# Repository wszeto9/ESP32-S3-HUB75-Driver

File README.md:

# ESP32-S3-HUB75-Driver

This board serves as the Matrix Display driver for MIT's 2.007 gameboards in Spring 2024 and Spring 2025. The board can take 4 button inputs, Stemma-QT I2C sensors, and breaks out 8 GPIO pins for future use. The board also features a ambient light sensor to adjust brightness in real time, as well as two buttons to switch modes if needed. The board supports USB-C PD power input up to 20V and USB debugging, as well as a 5.5mm OD / 2.1mm ID barrel jack for 9-24V input. A 5V/6A Buck converter helps ensure that the display is adequately powered. For this reason, it's recommended to power the display off a source higher than 5V for long term purposes. 

The board contains a power mux that automatically switches power sources based on what's present. It will always choose the first power source that's provided. If debugging is desired, it's recommended to first plug in the barrel jack for power, then use the USB port for debugging. This ensures lower power draw from the host computer. 

Upon power up, D7 or D9 will light up based on what power source is present. D2 should blink in accordance to the voltage of the power source (ie 5 blinks is a 5V source). D1 indicates that power is properly being delivered to the converter. 

At this point, the ESP32-S3 should pop up as a virtual COM port over USB. Boot and reset buttons are located by the ESP, but they may not be needed to perform DFU. 

Note: E8 and E16 refer to the pin that is used to act as pin E. This is only present on 64x64 pixel displays and larger. Some displays use pin 8, some displays use pin 16. Adafruit claims they use pin 8 for address E, so use a solder blob to jump the jumper to E8.

Further documentation can be found under the specific firmware builds.

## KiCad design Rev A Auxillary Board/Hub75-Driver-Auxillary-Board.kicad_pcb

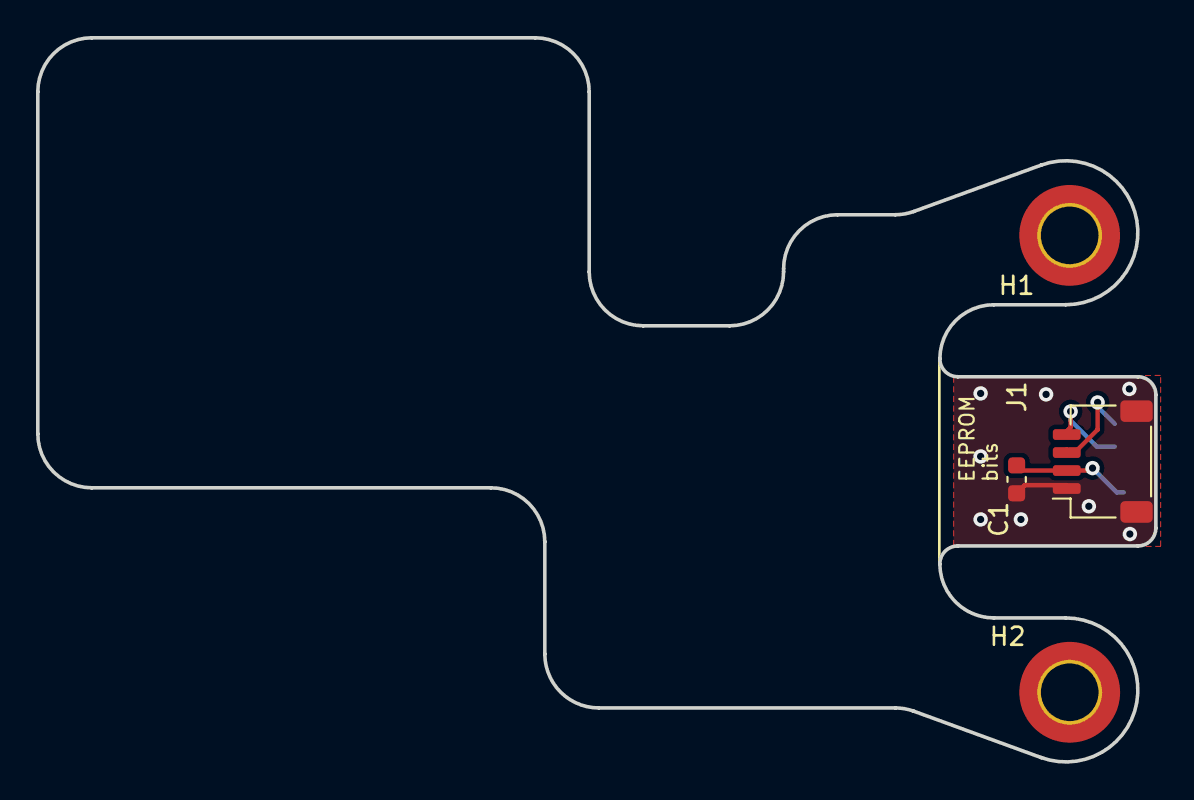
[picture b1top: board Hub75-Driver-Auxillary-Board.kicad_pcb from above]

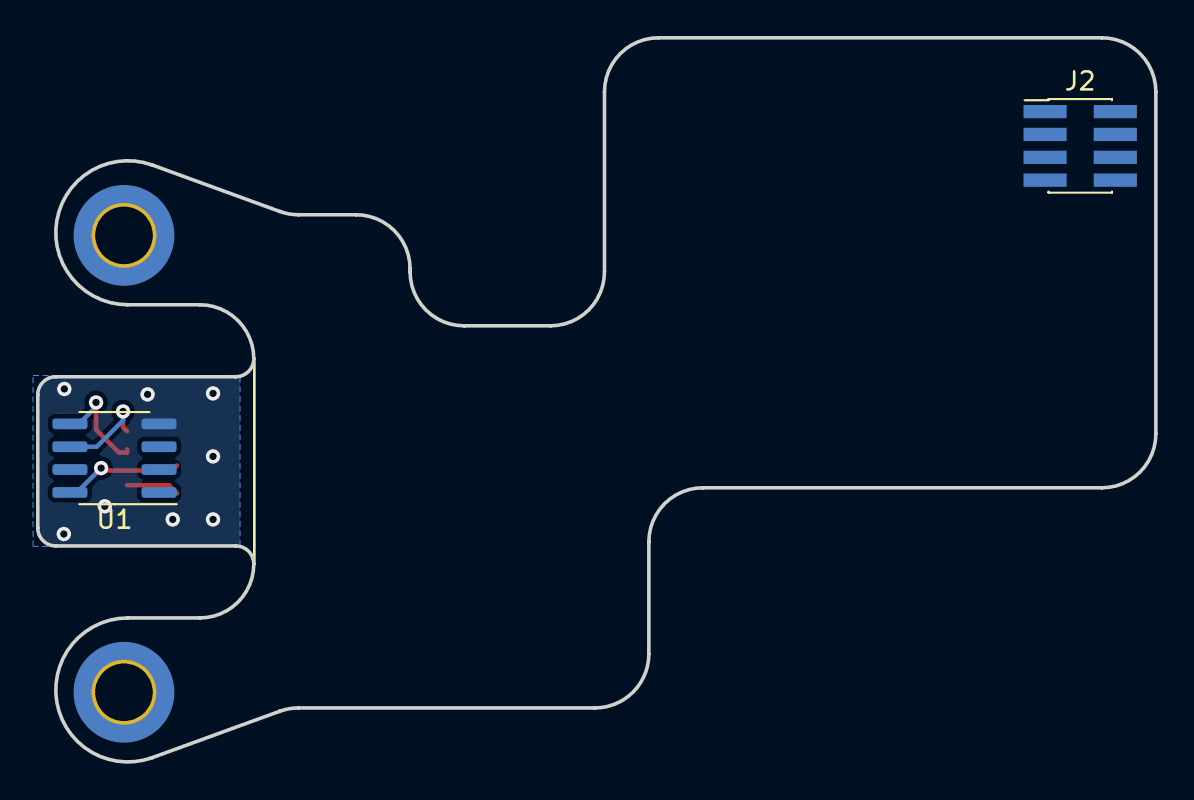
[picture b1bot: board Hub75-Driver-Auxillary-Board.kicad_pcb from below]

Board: 2 copper layers, 62.1 x 40.2 mm, 6 parts (2 on the bottom side), 4 nets.

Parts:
C1: 0603,100nF,50V,X7R; C_0603_1608Metric
H1, H2: MountingHole_Pad; MountingHole_3.2mm_M3_DIN965_Pad_TopBottom
J1: JST-SH-SM04B; JST_SH_SM04B-SRSS-TB_1x04-1MP_P1.00mm_Horizontal
J2: Conn_02x04_Odd_Even; PinHeader_2x04_P1.27mm_Vertical_SMD
U1: M24C01-FMN; SOIC-8_3.9x4.9mm_P1.27mm

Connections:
+5VD: C1.1, J1.2, U1.8 (VCC)
/SCL: J1.4, U1.6 (SCL)
/SDA: J1.3, U1.5 (SDA)
GNDS: C1.2, J1.1, J1.MP (MountPin), U1.4 (VSS)

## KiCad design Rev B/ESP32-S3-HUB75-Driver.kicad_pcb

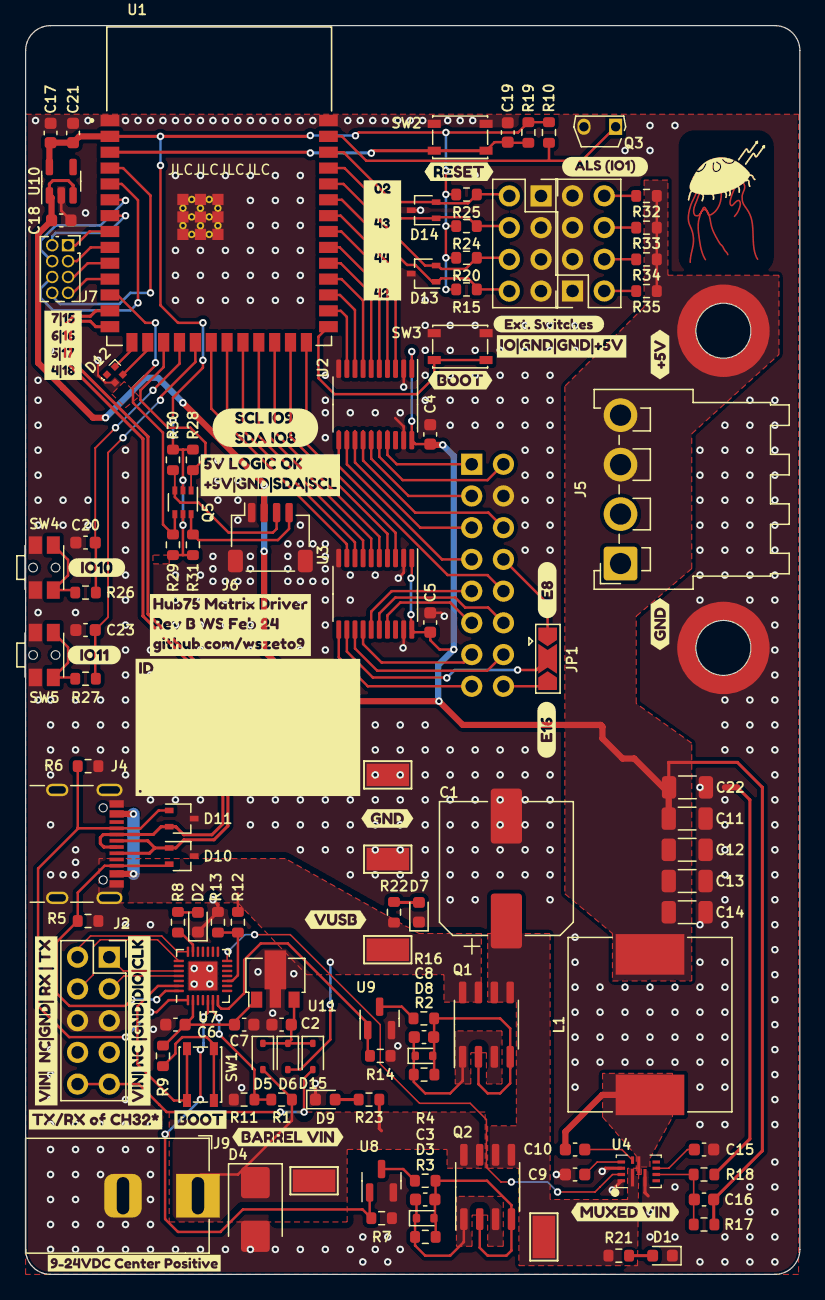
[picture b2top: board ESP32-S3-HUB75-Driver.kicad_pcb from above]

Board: 2 copper layers, 62.0 x 100.0 mm, 137 parts (1 on the bottom side), 100 nets.

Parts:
C1: 560uF/25V; CP_Elec_10x12.5
C2, C9, C19: 0603,1uF,50V,X5R; C_0603_1608Metric
C3, C4, C5, C6, C7, C8, C10, C15, C20, C21, C23: 0603,100nF,50V,X7R; C_0603_1608Metric
C11, C12, C13, C14, C22: 1206,22uF,25V,X5R; C_1206_3216Metric
C16: 0603,22pF,50V,C0G; C_0603_1608Metric
C17, C18: 0603,10uF,10V,X5R; C_0603_1608Metric
D1, D2, D7, D9: LED_White; LED_0603_1608Metric
D3, D8: BZT52C15T-7; D_SOD-523
D4: SMBJ24A; D_SMB
D5, D6, D15: 1N4148WS; D_SOD-323
D10, D11, D13, D14: SP0502BAJT; SOT-323_SC-70
D12: SK6805-EC15; LED_SK6812_EC15_1.5x1.5mm
H1, H2: WA-SMSI M3-H5mm; Mounting_Wuerth_WA-SMSI-M3_H5mm_9774050360
J1: 2x08 Pin Socket P2.54mm; PinSocket_2x08_P2.54mm_Vertical
J2: Conn_02x05_Odd_Even; PinSocket_2x05_P2.54mm_Vertical
J3, J8: 2x04 Socket P2.54mm; PinSocket_2x04_P2.54mm_Vertical
J4: USB4105; USB_C_Receptacle_GCT_USB4105-xx-A_16P_TopMnt_Horizontal
J5: S4P-VH; JST_VH_S4P-VH_1x04_P3.96mm_Horizontal
J6: JST-SH-SM04B; JST_SH_SM04B-SRSS-TB_1x04-1MP_P1.00mm_Horizontal
J7: 2x04 Socket P1.27mm; PinSocket_2x04_P1.27mm_Vertical
J9: Barrel_Jack; BarrelJack_Horizontal
JP1: EJumper; SolderJumper-3_P2.0mm_Open_TrianglePad1.0x1.5mm
L1: DR125-1R0-R; L_Sunlord_MWSA1206S-1R5
LOGO1: Logo
NT1: NetTie_2; NetTie-2_SMD_Pad0.5mm
Q1, Q2: DMP3036SSD; SO-8_3.9x4.9mm_P1.27mm
Q3: Q_Photo_NPN; TO-92S-2
Q5: BSS138BKS; SOT-363_SC-70-6
R1, R4, R12, R16, R19, R28, R29, R30, R31: 0603,10k; R_0603_1608Metric
R2, R3: 0603,100k; R_0603_1608Metric
R5, R6: 0603,5.1k; R_0603_1608Metric
R7, R8, R10, R11, R13, R14, R15, R20, R21, R22, R23, R24, R25: 0603,1k; R_0603_1608Metric
R9: 0603,4.7k; R_0603_1608Metric
R17, R26, R27: 0603,49.9k; R_0603_1608Metric
R18: 0603,6.8k; R_0603_1608Metric
R32, R33, R34, R35: 0603,0; R_0603_1608Metric
SW1, SW2, SW3: PTS810 SJM; SW_SPST_PTS810
SW4, SW5: EVQ-P7C01P; SW_SPST_EVQP7C
TP1, TP2, TP3, TP4, TP5: TestPoint; TestPoint_Keystone_5015_Micro-Minature
U1: ESP32-S3-WROOM-1-N16; XCVR_ESP32-S3-WROOM-1-N16R2
U2, U3: 74AHCT245PW,118; TSSOP-20_4.4x6.5mm_P0.65mm
U4: TPS51385RJNR; VQFN-HR12_RJN_TEX
U7: CH32X035G8U6; QFN-28-1EP_4x4mm_P0.4mm_EP2.3x2.3mm
U8, U9: AO3400A; SOT-23
U10: AP2112K-3.3; SOT-23-5
U11: L78L05_SOT89; SOT-89-3
kibuzzard-65AE10D9: G***; kibuzzard-65AE10D9
kibuzzard-65AE10E5: G***; kibuzzard-65AE10E5
kibuzzard-65AE16BC: G***; kibuzzard-65AE16BC
kibuzzard-65AE16C6: G***; kibuzzard-65AE16C6
kibuzzard-65AE17F6: G***; kibuzzard-65AE17F6
kibuzzard-65AE1571: G***; kibuzzard-65AE1571
kibuzzard-65AE1583: G***; kibuzzard-65AE1583
kibuzzard-65AE1804: G***; kibuzzard-65AE1804
kibuzzard-65BF1DC3: G***; kibuzzard-65BF1DC3
kibuzzard-65BF1E36: G***; kibuzzard-65BF1E36
kibuzzard-65BFF68F: G***; kibuzzard-65BFF68F
kibuzzard-65C14F52: G***; kibuzzard-65C14F52
kibuzzard-65C018C7: G***; kibuzzard-65C018C7
kibuzzard-65C018EB: G***; kibuzzard-65C018EB
kibuzzard-65C019AC: G***; kibuzzard-65C019AC
kibuzzard-65C027AA: G***; kibuzzard-65C027AA
kibuzzard-65C027DC: G***; kibuzzard-65C027DC
kibuzzard-65C028A7: G***; kibuzzard-65C028A7
kibuzzard-65C028B8: G***; kibuzzard-65C028B8
kibuzzard-65C150B0: G***; kibuzzard-65C150B0
kibuzzard-65C150D7: G***; kibuzzard-65C150D7
kibuzzard-65C1584F: G***; kibuzzard-65C1584F
kibuzzard-65C01916: G***; kibuzzard-65C01916
kibuzzard-65C01956: G***; kibuzzard-65C01956
kibuzzard-65C06362: G***; kibuzzard-65C06362
kibuzzard-65C15813: G***; kibuzzard-65C15813

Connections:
+3.3V: C17.1, C21.1, Q5.2 (G), Q5.5 (G), R10.1, R15.2, R19.1, R20.2, R24.2, R25.2, R28.1, R29.1, R30.1, R31.1, U1.2 (3V3), U10.5 (VOUT)
+5V: C4.1, C5.1, C11.1, C12.1, C13.1, C14.1, C16.1, C18.1, C22.1, H1.1, J5.3, J5.4, J6.2, L1.2, R17.1, R32.2, R33.2, R34.2, R35.2, U2.1 (DIR), U2.20 (VCC), U3.1 (DIR), U3.20 (VCC), U10.1 (VIN), U10.3 (EN)
/5V6A Buck/BuckEna: U4.11 (EN), U7.14 (PB3)
/A: J1.9, U3.15 (B3)
/ADDRA_3V: U1.24 (IO47), U3.5 (A3)
/ADDRB_3V: U1.28 (IO35), U2.9 (A7)
/ADDRC_3V: U1.26 (IO45), U3.3 (A1)
/ADDRD_3V: U1.25 (IO48), U3.4 (A2)
/ADDRE_3V: U1.21 (IO13/SDI), U3.8 (A6)
/B: J1.10, U2.11 (B7)
/B1: J1.3, U2.15 (B3)
/B1_3V: U1.32 (IO39), U2.5 (A3)
/B2: J1.7, U2.12 (B6)
/B2_3V: U1.29 (IO36), U2.8 (A6)
/C: J1.11, U3.17 (B1)
/CLK: J1.13, U3.14 (B4)
/CLK_3V: U1.23 (IO21), U3.6 (A4)
/D: J1.12, U3.16 (B2)
/E: JP1.2 (C), U3.12 (B6)
/E8: J1.8, JP1.1 (A)
/E16: J1.16, JP1.3 (B)
/ESP_USB_N: D11.2 (K), J4.A7 (D-), J4.B7 (D-), U1.13 (IO19)
/ESP_USB_P: D10.1 (K), J4.A6 (D+), J4.B6 (D+), U1.14 (IO20)
/G1: J1.2, U2.16 (B2)
/G1_3V: U1.33 (IO40), U2.4 (A2)
/G2: J1.6, U2.14 (B4)
/G2_3V: U1.31 (IO38), U2.6 (A4)
/IO0: SW3.2 (B), U1.27 (IO0)
/IO1: Q3.1 (C), R10.2, U1.39 (IO1)
/IO2: D14.2 (K), J8.2, R25.1, U1.38 (IO2)
/IO4: J7.8, U1.4 (IO4)
/IO5: J7.6, U1.5 (IO5)
/IO6: J7.4, U1.6 (IO6)
/IO7: J7.2, U1.7 (IO7)
/IO10: C20.1, R26.2, U1.18 (IO10/CS)
/IO11: C23.1, R27.2, U1.19 (IO11/SDO)
/IO15: J7.1, U1.8 (IO15)
/IO16: J7.3, U1.9 (IO16)
/IO17: J7.5, U1.10 (IO17)
/IO18: J7.7, U1.11 (IO18)
/IO42: D13.1 (K), J8.8, R15.1, U1.35 (IO42)
/IO43: D14.1 (K), J8.4, R24.1, U1.37 (TXD0)
/IO44: D13.2 (K), J8.6, R20.1, U1.36 (RXD0)
/LAT: J1.14, U3.13 (B5)
/LAT_3V: U1.22 (IO14), U3.7 (A5)
/NEOPX_DATA: D12.3 (DIN), U1.16 (IO46)
/NEOPX_PWR: D12.4 (VDD), U1.15 (IO3)
/OE: J1.15, U3.11 (B7)
/OE_3V: U1.20 (IO12/CLK), U3.9 (A7)
/Power and USB Inputs/5V_PROG: D15.2 (A), J2.9, J2.10
/Power and USB Inputs/CC1: D11.1 (K), J4.A5 (CC1), R6.2, U7.1 (PC15/CC2)
/Power and USB Inputs/CC2: D10.2 (K), J4.B5 (CC2), R5.2, U7.28 (PC14/CC1)
/Power and USB Inputs/CH32_RX: J2.4, U7.22 (PB11)
/Power and USB Inputs/CH32_TX: J2.2, U7.21 (PB10)
/Power and USB Inputs/CommonSourceBarrel: C3.1, D3.1 (K), Q2.1 (S), Q2.3 (S), R3.1
/Power and USB Inputs/CommonSource_USBCPower: C8.1, D8.1 (K), Q1.1 (S), Q1.3 (S), R2.1
/Power and USB Inputs/ENA_BARREL: R7.1, U7.5 (PA0), U8.1 (G)
/Power and USB Inputs/ENA_USBPD: R14.1, U7.7 (PA2), U9.1 (G)
/Power and USB Inputs/Gate_Barrel: C3.2, D3.2 (A), Q2.2 (G), Q2.4 (G), R3.2, R4.1
/Power and USB Inputs/Gate_USBCPower: C8.2, D8.2 (A), Q1.2 (G), Q1.4 (G), R2.2, R16.1
/Power and USB Inputs/SWDCLK: J2.1, U7.24 (PC19/DCK)
/Power and USB Inputs/SWDIO: J2.3, U7.25 (PC18/DIO)
/Power and USB Inputs/USB_CH32_P: SW1.1 (A), U7.27 (PC17/UDP)
/Power and USB Inputs/VCC_CH32: C6.1, C7.1, R9.1, U7.2 (VDD), U11.1 (OUT)
/Power and USB Inputs/VIN_BARREL: D4.1 (K), D5.2 (A), J9.1, Q2.7 (D), Q2.8 (G), R1.1, R23.1, TP3.1
/Power and USB Inputs/VSENSE_BARREL: R1.2, R11.1, U7.6 (PA1)
/Power and USB Inputs/VSENSE_USBPD: R12.2, R13.1, U7.10 (PA5)
/Power and USB Inputs/VUSBC: D6.2 (A), J4.A4 (VBUS), J4.A9 (VBUS), J4.B4 (VBUS), J4.B9 (VBUS), Q1.7 (D), Q1.8 (G), R12.1, R22.1, TP2.1
/R1: J1.1, U2.17 (B1)
/R1_3V: U1.34 (IO41), U2.3 (A1)
/R2: J1.5, U2.13 (B5)
/R2_3V: U1.30 (IO37), U2.7 (A5)
/SCL: Q5.1 (S), R28.2, U1.17 (IO9/SCL)
/SCL_EXT: J6.4, Q5.6 (D), R31.2
/SDA: Q5.4 (S), R29.2, U1.12 (IO8/SDA)
/SDA_EXT: J6.3, Q5.3 (D), R30.2
/VIN_MUXED: C1.1, Q1.5 (D), Q1.6 (G), Q2.5 (D), Q2.6 (G), R21.1, TP1.1, U4.1 (VIN)
/~RST: C19.1, R19.2, SW2.2 (B), U1.3 (EN)
GND: C1.2, C2.2, C4.2, C5.2, C6.2, C7.2, C9.2, C11.2, C12.2, C13.2, C14.2, C15.2, C17.2, C18.2, C19.2, C20.2, C21.2, C22.2, C23.2, D1.1 (K), D2.1 (K), D4.2 (A), D7.1 (K), D9.1 (K), D10.3 (A), D11.3 (A), D12.2 (VSS), D13.3 (A), D14.3 (A), H2.1, J1.4, J2.5, J2.6, J3.1, J3.3, J3.5, J3.7, J4.A1 (GND), J4.A12 (GND), J4.B1 (GND), J4.B12 (GND), J4.S1 (SHIELD), J5.1, J5.2, J6.1, J6.MP (MountPin), J8.1, J8.3, J8.5, J8.7, J9.2, NT1.1, Q3.2 (E), R5.1, R6.1, R7.2, R11.2, R13.2, R14.2, SW2.1 (A), SW3.1 (A), SW4.2 (B), SW5.2 (B), TP4.1, TP5.1, U1.1 (GND), U1.40 (GND), U1.41_1 (GND), U1.41_2 (GND), U1.41_3 (GND), U1.41_4 (GND), U1.41_5 (GND), U1.41_6 (GND), U1.41_7 (GND), U1.41_8 (GND), U1.41_9 (GND), U1.41_10 (GND), U1.41_11 (GND), U1.41_12 (GND), U1.41_13 (GND), U1.41_14 (GND), U1.41_15 (GND), U1.41_16 (GND), U1.41_17 (GND), U1.41_18 (GND), U1.41_19 (GND), U1.41_20 (GND), U1.41_21 (GND), U2.2 (A0), U2.10 (GND), U2.19 (~OE), U3.2 (A0), U3.10 (GND), U3.19 (~OE), U4.2 (PGND), U4.10 (AGND), U4.12 (MODE), U7.29 (GND), U8.2 (S), U9.2 (S), U10.2 (GND), U11.2 (GND)
unnamed: D1.2 (A), R21.2
unnamed: D2.2 (A), R8.2
unnamed: D7.2 (A), R22.2
unnamed: D9.2 (A), R23.2
unnamed: C2.1, D5.1 (K), D6.1 (K), D15.1 (K), U11.3 (IN)
unnamed: J3.2, R35.1
unnamed: J3.4, R34.1
unnamed: J3.6, R33.1
unnamed: J3.8, R32.1
unnamed: NT1.2, R18.2
unnamed: R9.2, SW1.2 (B)
unnamed: R26.1, SW4.1 (A)
unnamed: R27.1, SW5.1 (A)
unnamed: C16.2, R17.2, R18.1, U4.4 (FB)
unnamed: C15.1, U4.5 (SS)
unnamed: C10.2, L1.1, U4.7 (SW)
unnamed: C10.1, U4.8 (VBST)
unnamed: C9.1, U4.9 (VCC)
unnamed: R8.1, U7.20 (PB9)
unnamed: R4.2, U8.3 (D)
unnamed: R16.2, U9.3 (D)

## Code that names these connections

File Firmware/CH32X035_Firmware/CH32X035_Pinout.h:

#ifdef REV_A01

#define PD_EN PA2
#define PD_SENSE PA3
#define BARREL_EN PA0
#define BARREL_SENSE PA1
#define BUCK_EN PB3
#define LED_BUILTIN PB12

#endif

#ifdef REV_A02

#define PD_EN PA2
#define PD_SENSE PA5
#define BARREL_EN PA0
#define BARREL_SENSE PA1
#define BUCK_EN PB3
#define LED_BUILTIN PB12

#endif

#ifdef REV_B01

#define PD_EN PA2
#define PD_SENSE PA5
#define BARREL_EN PA0
#define BARREL_SENSE PA1
#define BUCK_EN PB3
#define LED_BUILTIN PB9

#endif

#ifdef REV_B02

  #define PD_EN PA2
  #define PD_SENSE PA5
  #define BARREL_EN PA0
  #define BARREL_SENSE PA1
  #define BUCK_EN PB3
  #define LED_BUILTIN PB9
  #define SenseDividerRatio 10

#endif

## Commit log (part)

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2024-01-28 laid out
2024-02-03 wrote fw
2024-02-03 updated schematic to look neater
2024-02-03 restructured folders
2024-02-07 added B01
2024-02-07 ignore unused files
2024-02-07 added LED test for CH32X035 fw
2024-02-07 Test for doing timer interrupts on ESP32 S3
2024-02-12 Added documentation for A02 rework
2024-02-12 added firmware
2024-02-14 added logos to UI
2024-02-14 B02: edited passive values
    HSS slew rate edited by replacing slew-rate limiting capacitor to 4.7uF/35V
    24V LED resistor changed to 10K to not burn an LED
    Resistor divider for voltage sense edited to 18K/3,3K
2024-02-14 added revision-based pin definitions
2024-03-02 Created fw for spaceship (2.007)
2024-03-02 Added automatic power input switching
2024-03-02 Added divider ratio for sense circuit by hardware revisions
2024-03-02 added button support
2024-03-18 Created Visual Assets
2024-03-18 Added visuals for no accel on shapeship
2024-03-18 Added graphic for disconnected switches
2024-03-18 Added graphics on buttons display
2024-03-18 added frontend to spaceship display
2024-03-20 Started Auxillary Board
2024-04-02 added detection for switches not connected
2024-04-02 Added brightness feedback
2025-03-06 idk man seems like old code I didn't commit
2025-03-06 Added GameboardButtons.drawio
2025-03-06 added documentation
2025-03-06 start the 2025 gameboard fw
2025-03-06 GameboardLevers.drawio
2025-03-06 visuals
2025-03-18 timer updated for 3.0.x ESP32 API support
2025-04-01 Button Template Code
    Trial Code Seprate from the Gameboard code for the buttons
2025-04-03 4/2 Work
    - horizontal letters
    - trying to get button interrupt to work
2025-04-16 idk
    april 16
2025-04-25 it works!
    this code works
